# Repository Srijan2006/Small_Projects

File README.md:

#**These projects may not reflect 100% of my knowledge — they are samples, snapshots of where I started and what I've been learning.
But this is not the end — it's just the beginning. I’m committed to growing, improving, and building better projects ahead**

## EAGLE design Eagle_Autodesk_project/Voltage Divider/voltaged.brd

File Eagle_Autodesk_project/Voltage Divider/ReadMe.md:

# Voltage Divider Circuit

This project showcases a **Voltage Divider**, one of the most fundamental and versatile building blocks in electronics. Using two resistors in series, the circuit divides input voltage into a lower output voltage.

## Features
- Simple voltage level adjustment
- Customizable resistor ratios
- Ideal for signal scaling

## Components
- 2 resistors (R1, R2)
- Power supply
- Optional: Load resistor for testing

## Applications
- Analog sensors
- Level shifting
- Biasing transistors

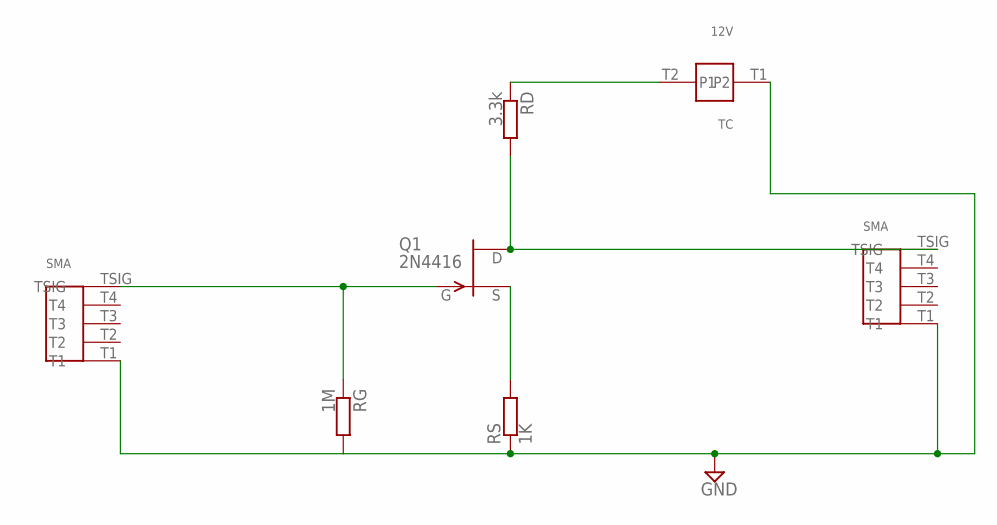
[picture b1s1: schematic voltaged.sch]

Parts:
Q1: 2N4416; TO72
RD: 3.3k; SMR-0
RG: 1M; SMR-0
RS: 1K; SMR-0
U$1, U$2, U$3: TC

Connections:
GND: RG.1, RS.2, U$1.T1 (P1), U$2.T1, U$3.T1
unnamed: Q1.3 (G), RG.2, U$2.TSIG
unnamed: Q1.1 (S), RS.1
unnamed: Q1.2 (D), RD.1, U$3.TSIG
unnamed: RD.2, U$1.T2 (P2)

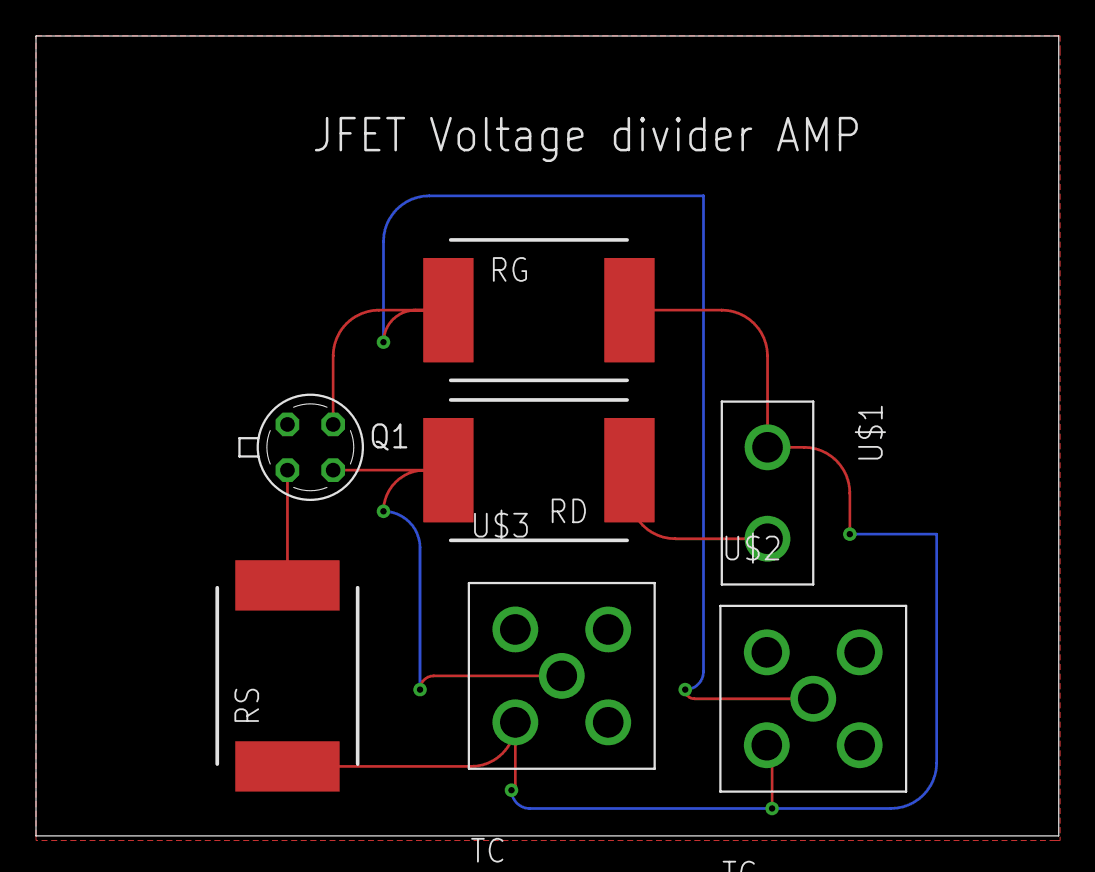
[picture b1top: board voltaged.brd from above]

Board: 2 copper layers, 56.8 x 44.4 mm, 7 parts (0 on the bottom side), 5 nets.

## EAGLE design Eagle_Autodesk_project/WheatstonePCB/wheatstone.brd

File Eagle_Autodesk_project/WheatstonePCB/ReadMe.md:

# Wheatstone Bridge Circuit

This project demonstrates a **Wheatstone Bridge**, a classic configuration used to precisely measure unknown resistances. The bridge consists of four resistors arranged in a diamond shape, with voltage applied across the bridge and a galvanometer used to detect balance.

## Features
- Precision resistance measurement
- Adjustable resistor for balancing the bridge
- Useful for strain gauge applications

## Components
- 4 resistors (R1, R2, R3, Rx)
- Power supply
- Optional: Potentiometer for R3 or R4

## Applications
- Sensor calibration
- Instrumentation
- Analog circuit experimentation

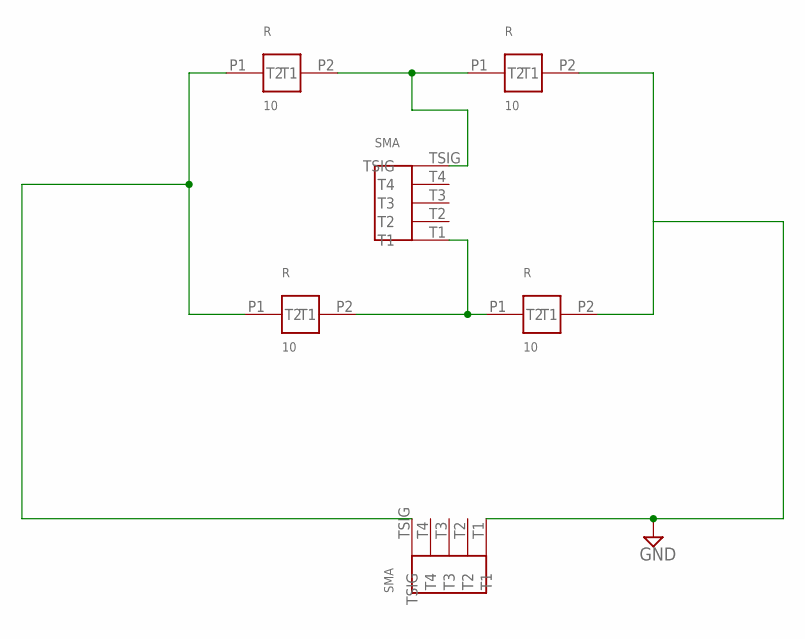
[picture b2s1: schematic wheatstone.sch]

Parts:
U$1, U$2, U$3, U$4: 0404RESISTORS
U$5, U$6: TC

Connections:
GND: U$2.P2 (T2), U$4.P2 (T2), U$6.T1
unnamed: U$1.P1 (T1), U$3.P1 (T1), U$6.TSIG
unnamed: U$1.P2 (T2), U$2.P1 (T1), U$5.TSIG
unnamed: U$3.P2 (T2), U$4.P1 (T1), U$5.T1

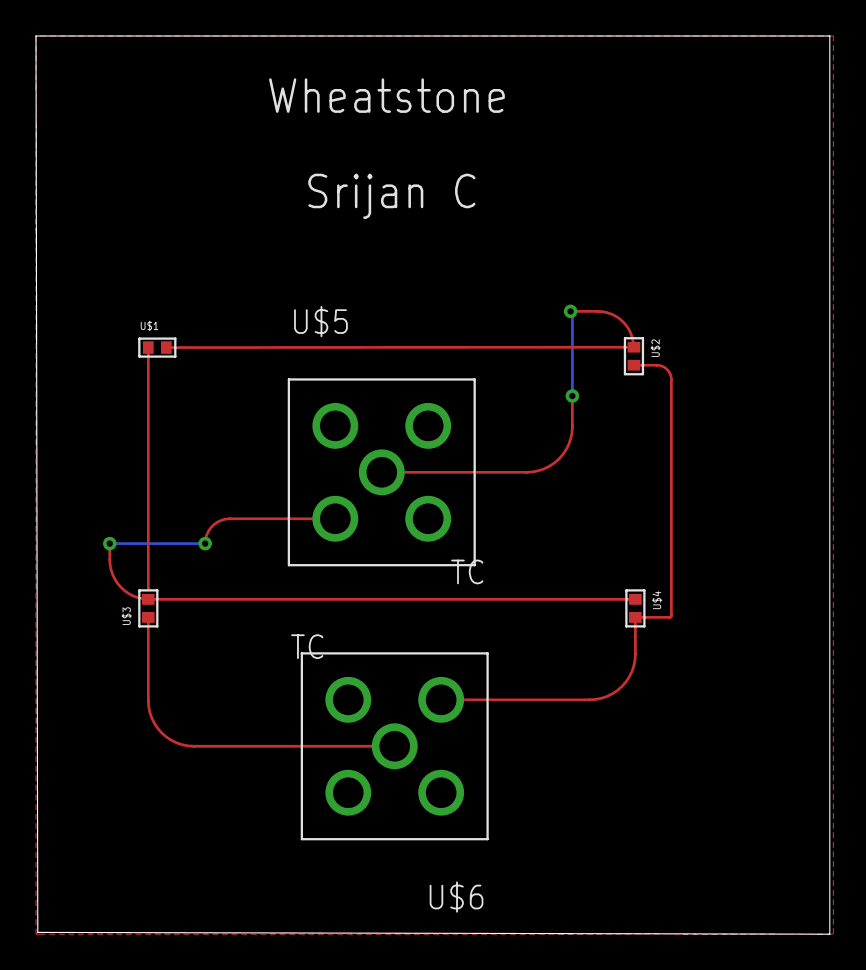
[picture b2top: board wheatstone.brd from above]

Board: 2 copper layers, 44.1 x 49.9 mm, 6 parts (0 on the bottom side), 4 nets.

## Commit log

2025-07-11 MY SMALL Projects
